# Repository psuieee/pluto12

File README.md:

# pluto12 Macropad

The pluto12 is a 4x3 macropad designed for use in the Penn State IEEE Student Chapter's [2021-22 workshop series](https://github.com/psuieee/projects2021). Designed by the 2021-22 Penn State IEEE Projects Committee.

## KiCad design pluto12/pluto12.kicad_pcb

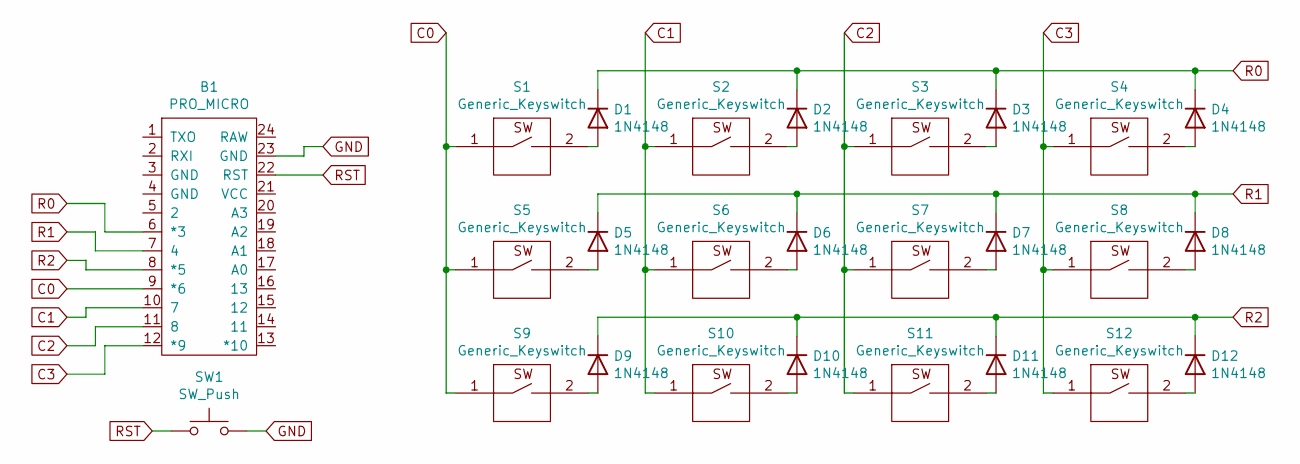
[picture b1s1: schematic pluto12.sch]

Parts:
B1: PRO_MICRO; Pro-Micro
D1, D2, D3, D4, D5, D6, D7, D8, D9, D10, D11, D12: 1N4148; D_DO-35_SOD27_P7.62mm_Horizontal
S1, S2, S3, S4, S5, S6, S7, S8, S9, S10, S11, S12: Generic_Keyswitch; SW_Cherry_MX_1.00u_PCB_centered
SW1: SW_Push; SW_SPST_EVPBF

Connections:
C0: B1.9 (*6), S1.1, S5.1, S9.1
C1: B1.10 (7), S2.1, S6.1, S10.1
C2: B1.11 (8), S3.1, S7.1, S11.1
C3: B1.12 (*9), S4.1, S8.1, S12.1
GND: B1.23 (GND), SW1.2; also elsewhere on the board
unnamed: D1.2 (A), S1.2
unnamed: D2.2 (A), S2.2
unnamed: D3.2 (A), S3.2
unnamed: D4.2 (A), S4.2
unnamed: D5.2 (A), S5.2
unnamed: D6.2 (A), S6.2
unnamed: D7.2 (A), S7.2
unnamed: D8.2 (A), S8.2
unnamed: D9.2 (A), S9.2
unnamed: D10.2 (A), S10.2
unnamed: D11.2 (A), S11.2
unnamed: D12.2 (A), S12.2
R0: B1.6 (*3), D1.1 (K), D2.1 (K), D3.1 (K), D4.1 (K)
R1: B1.7 (4), D5.1 (K), D6.1 (K), D7.1 (K), D8.1 (K)
R2: B1.8 (*5), D9.1 (K), D10.1 (K), D11.1 (K), D12.1 (K)
RST: B1.22 (RST), SW1.1; also elsewhere on the board

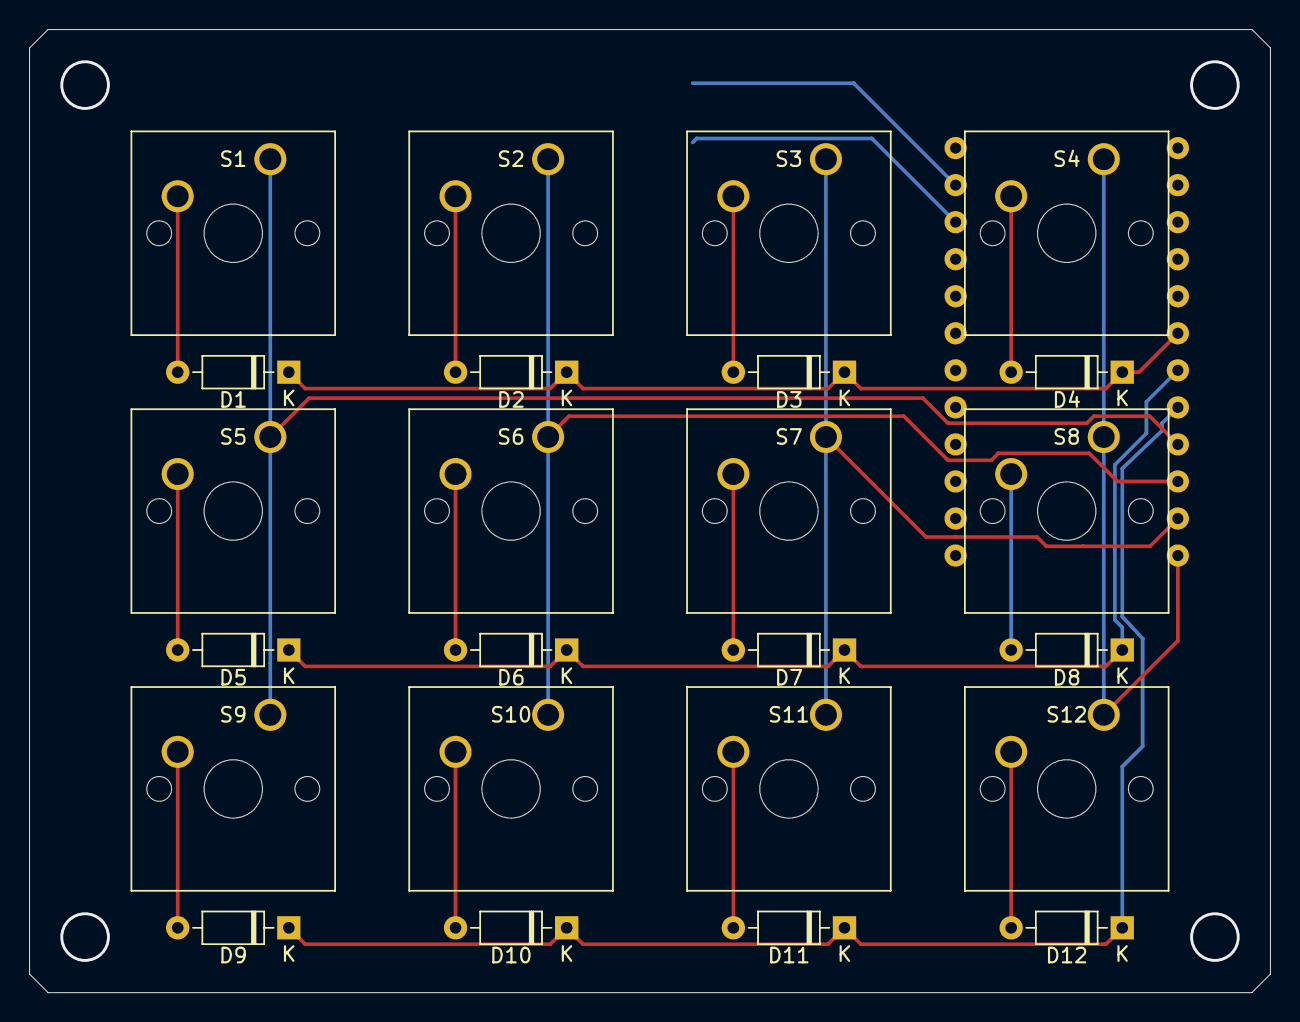
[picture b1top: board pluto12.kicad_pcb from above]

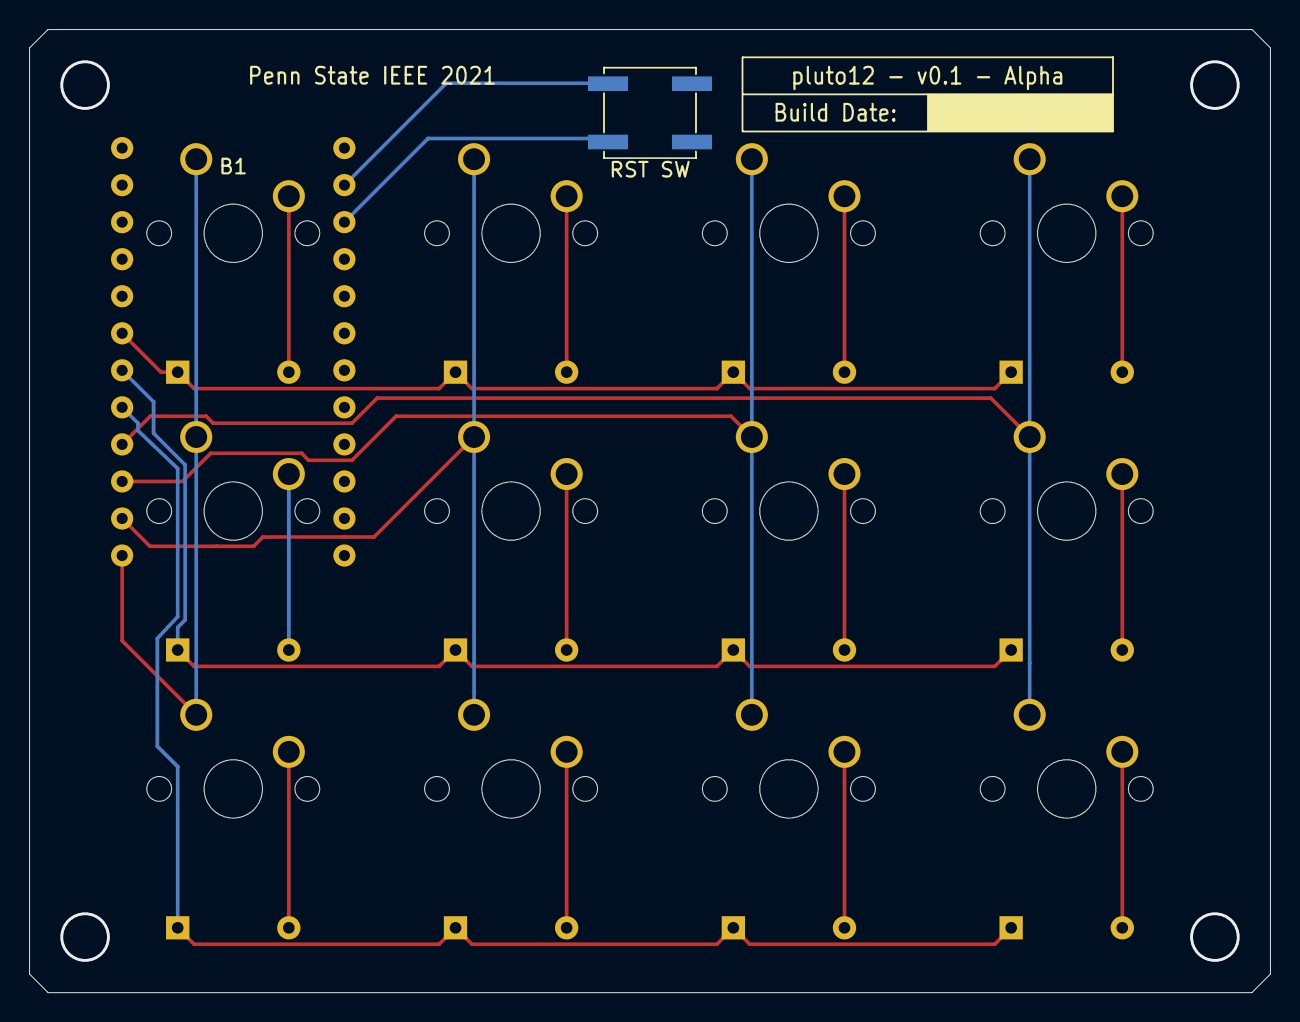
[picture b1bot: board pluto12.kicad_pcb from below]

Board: 2 copper layers, 85.1 x 66.0 mm, 26 parts (2 on the bottom side), 21 nets.

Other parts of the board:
RST SW: SW_Push; SW_SPST_EVPBF

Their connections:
GND: RST SW.2; also elsewhere on the board
RST: RST SW.1; also elsewhere on the board

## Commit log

2021-10-02 Initial KiCad Project commit
2021-10-07 Key matrix and footprints update
    Key matrix from Noah; Footprints + symbols from Ethan
2021-10-31 v0.1 - Alpha commit
    Library rework for relative paths, keyswitch matrix fixes, added specific diode component. Initial board layout complete (thank you Amal!)
2021-11-05 v0.1a Version Upload
    - Edits to back silkscreen, border, and part labels on PCB.
    - Libraries reverted back to ${KIPRMOD}
